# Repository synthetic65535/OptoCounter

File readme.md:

# OptoCounter
Электронный счетчик импульсов.

* Используемый микроконтроллер: atmega8
* Среда разработки: KiCad
* Прошивка для микроконтроллера: [Здесь](https://github.com/synthetic65535/OptoCounterFirmware)

Отличительные особенности счетчика:
 * Возможность использовать самые разнообразные датчики, изменяющие во время работы свою проводимость: фоторезисторы, фототранзисторы, микрофоны...
 * Аппаратный фильтр, заглушающий помехи от 50 герц и выше
 * Аппаратный дифференциатор + компаратор с гистерезисом. При необходимости можно сделать подстройку схемы под конкретный датчик не изменяя прошивку микроконтроллера. Микроконтроллер не занимается фильтрацией сигнала, ему на вход подаются уже готовые прямоугольные импульсы, которые он считает.
 * Отсутствие SMD деталей
 * Питание от USB

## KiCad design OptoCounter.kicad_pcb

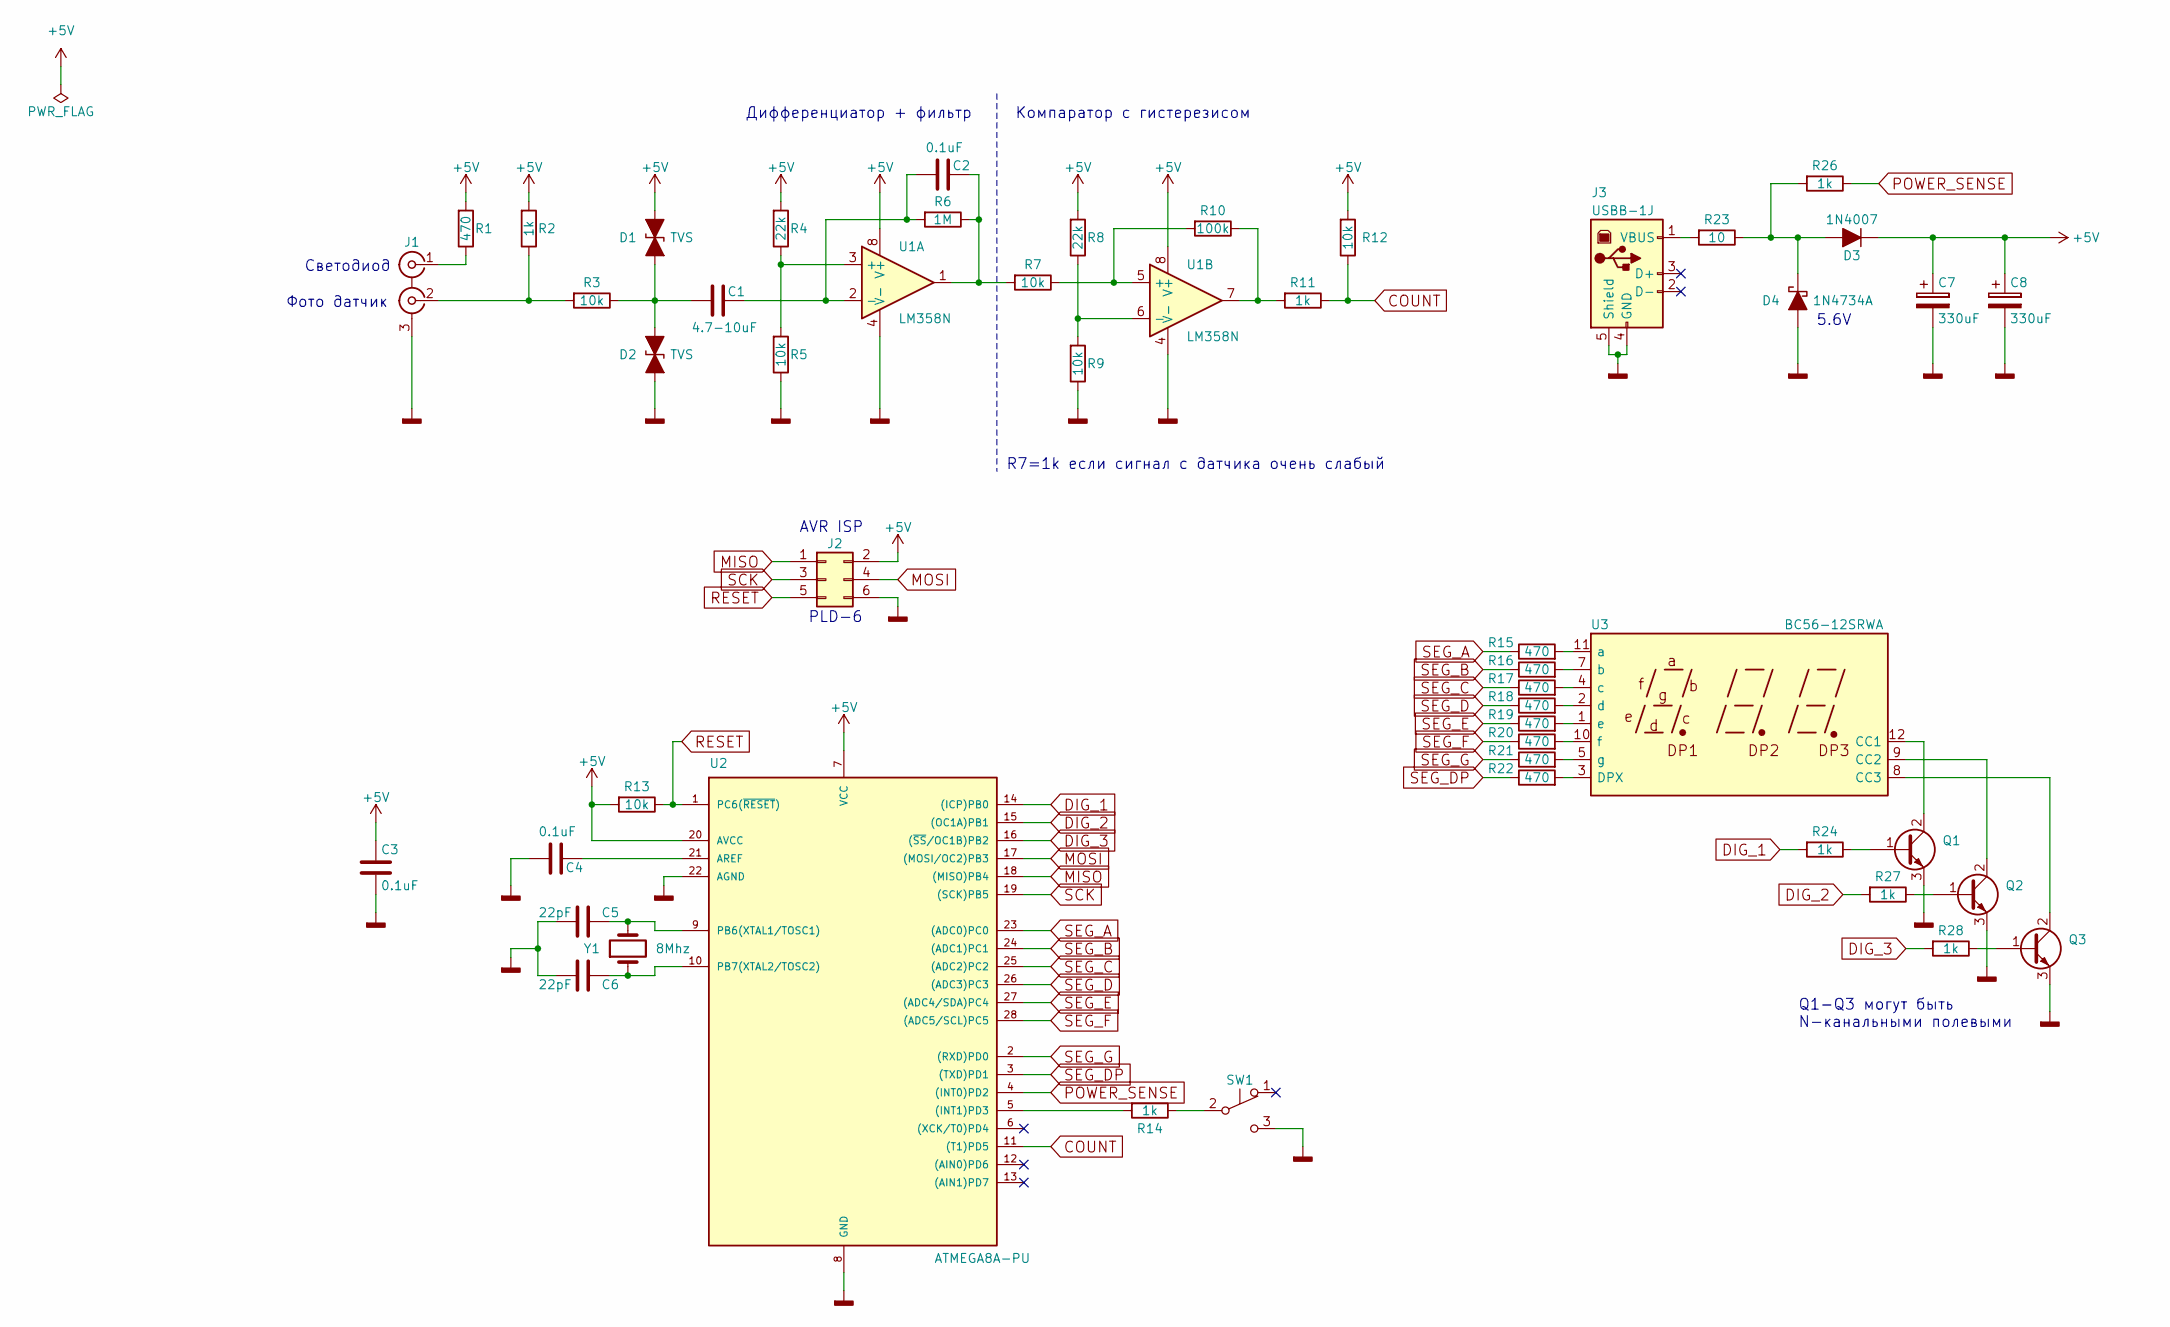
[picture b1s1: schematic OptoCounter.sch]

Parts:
C1: 4.7-10uF; CAP
C2, C3, C4: 0.1uF; CAP
C5, C6: 22pF; CAP
C7, C8: 330uF; CP_Radial_D6.3mm_P2.50mm
D1, D2: TVS; DO-41
D3: 1N4007; DO-41
D4: 1N4734A; DO-41
J1: RS-212; RS212
J2: PLD-6; AVR_ISP
J3: USBB-1J; USB_B
Q1, Q2, Q3: Q_NPN_BCE; Q_BCE
R1, R15, R16, R17, R18, R19, R20, R21, R22: 470; RES
R2, R11, R14, R24, R26, R27, R28: 1k; RES
R3, R5, R7, R9, R12, R13: 10k; RES
R4, R8: 22k; RES
R6: 1M; RES
R10: 100k; RES
R23: 10; RES
SW1: MSW-11; SM5-00N-115
U1: LM358N; DIP-8_W7.62mm_Socket
U2: ATMEGA8A-PU; TRS-28_Connfly
U3: BC56-12SRWA
Y1: 8Mhz; Crystal_HC49-4H_Vertical

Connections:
+5V: C3.1, C7.1, C8.1, D1.1 (A1), D3.1 (K), J2.2, R1.2, R2.2, R4.2, R8.2, R12.2, R13.2, U1.8 (V+), U2.7 (VCC), U2.20 (AVCC)
COUNT: R11.1, R12.1, U2.11 ((T1)PD5)
DIG_1: R24.2, U2.14 ((ICP)PB0)
DIG_2: R27.2, U2.15 ((OC1A)PB1)
DIG_3: R28.2, U2.16 ((~SS~/OC1B)PB2)
GNDD: C3.2, C4.2, C5.2, C6.2, C7.2, C8.2, D2.2 (A2), D4.2 (A), J1.3 (EXT), J2.6, J3.4 (GND), J3.5 (Shield), Q1.3 (E), Q2.3 (E), Q3.3 (E), R5.1, R9.1, SW1.3 (C), U1.4 (V-), U2.8 (GND), U2.22 (AGND)
MISO: J2.1, U2.18 ((MISO)PB4)
MOSI: J2.4, U2.17 ((MOSI/OC2)PB3)
unnamed: C1.1, C2.2, R6.2, U1.2 (-)
unnamed: C1.2, D1.2 (A2), D2.1 (A1), R3.1
unnamed: C2.1, R6.1, R7.2, U1.1
unnamed: C4.1, U2.21 (AREF)
unnamed: C5.1, U2.9 (PB6(XTAL1/TOSC1)), Y1.2
unnamed: C6.1, U2.10 (PB7(XTAL2/TOSC2)), Y1.1
unnamed: D3.2 (A), D4.1 (K), R23.1, R26.2
unnamed: J1.1 (IN1), R1.1
unnamed: J1.2 (IN2), R2.1, R3.2
unnamed: J3.1 (VBUS), R23.2
unnamed: Q1.1 (B), R24.1
unnamed: Q1.2 (C), U3.12 (CC1)
unnamed: Q2.1 (B), R27.1
unnamed: Q2.2 (C), U3.9 (CC2)
unnamed: Q3.1 (B), R28.1
unnamed: Q3.2 (C), U3.8 (CC3)
unnamed: R4.1, R5.2, U1.3 (+)
unnamed: R8.1, R9.2, U1.6 (-)
unnamed: R10.1, R11.2, U1.7
unnamed: R7.1, R10.2, U1.5 (+)
unnamed: R14.1, SW1.2 (B)
unnamed: R14.2, U2.5 ((INT1)PD3)
unnamed: R15.2, U3.11 (a)
unnamed: R16.2, U3.7 (b)
unnamed: R17.2, U3.4 (c)
unnamed: R18.2, U3.2 (d)
unnamed: R19.2, U3.1 (e)
unnamed: R20.2, U3.10 (f)
unnamed: R21.2, U3.5 (g)
unnamed: R22.2, U3.3 (DPX)
POWER_SENSE: R26.1, U2.4 ((INT0)PD2)
RESET: J2.5, R13.1, U2.1 (PC6(~RESET~))
SCK: J2.3, U2.19 ((SCK)PB5)
SEG_A: R15.1, U2.23 ((ADC0)PC0)
SEG_B: R16.1, U2.24 ((ADC1)PC1)
SEG_C: R17.1, U2.25 ((ADC2)PC2)
SEG_D: R18.1, U2.26 ((ADC3)PC3)
SEG_DP: R22.1, U2.3 ((TXD)PD1)
SEG_E: R19.1, U2.27 ((ADC4/SDA)PC4)
SEG_F: R20.1, U2.28 ((ADC5/SCL)PC5)
SEG_G: R21.1, U2.2 ((RXD)PD0)

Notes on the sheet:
Фото датчик
R7=1k если сигнал с датчика очень слабый
Компаратор с гистерезисом
Дифференциатор + фильтр
Светодиод
PLD-6
AVR ISP
5.6V
Q1-Q3 могут быть N-канальными полевыми

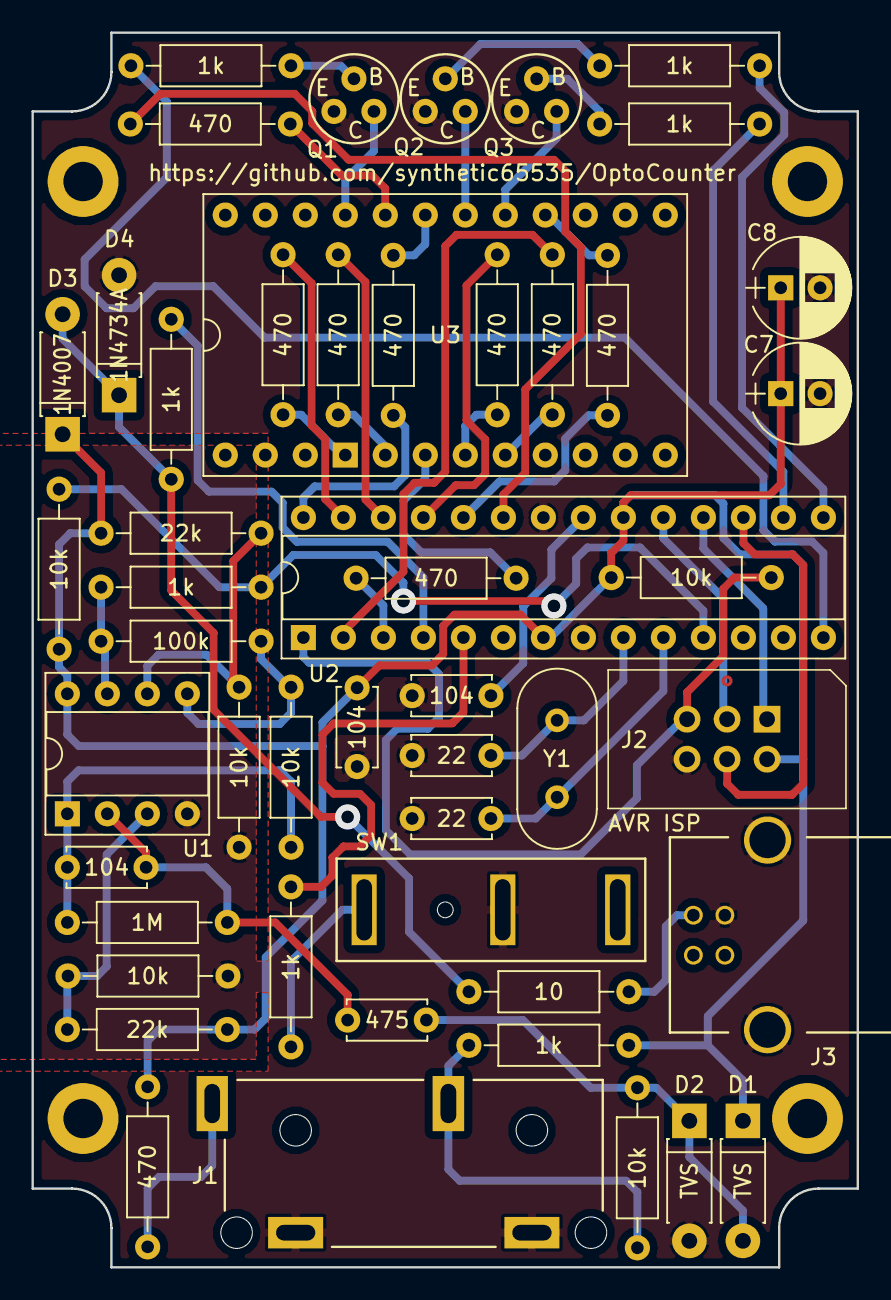
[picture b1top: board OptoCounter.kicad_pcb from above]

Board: 2 copper layers, 52.4 x 78.4 mm, 50 parts (0 on the bottom side), 49 nets.
